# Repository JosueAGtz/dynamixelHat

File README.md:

# RaspberryPi Dynamixel Hat

The Raspberry Pi Zero Dynamixel Hat it's an easy to use hardware that allows you to connect and communicate with Dynamixel Servo Motors by using the Savage Electronics AX interface circuit, providing the half-duplex communication needed by these motors, its implemented in it a voltage converter for all the signals to the Raspberry allowing a secure communication in terms of logical levels.

It also implements a MAX25232ATCG/V+ which is a synchronous step-down DC-DC converter optimized for applications with high power density, This regulator will let you power your Raspberry directly from a battery and also provide power to your motors.

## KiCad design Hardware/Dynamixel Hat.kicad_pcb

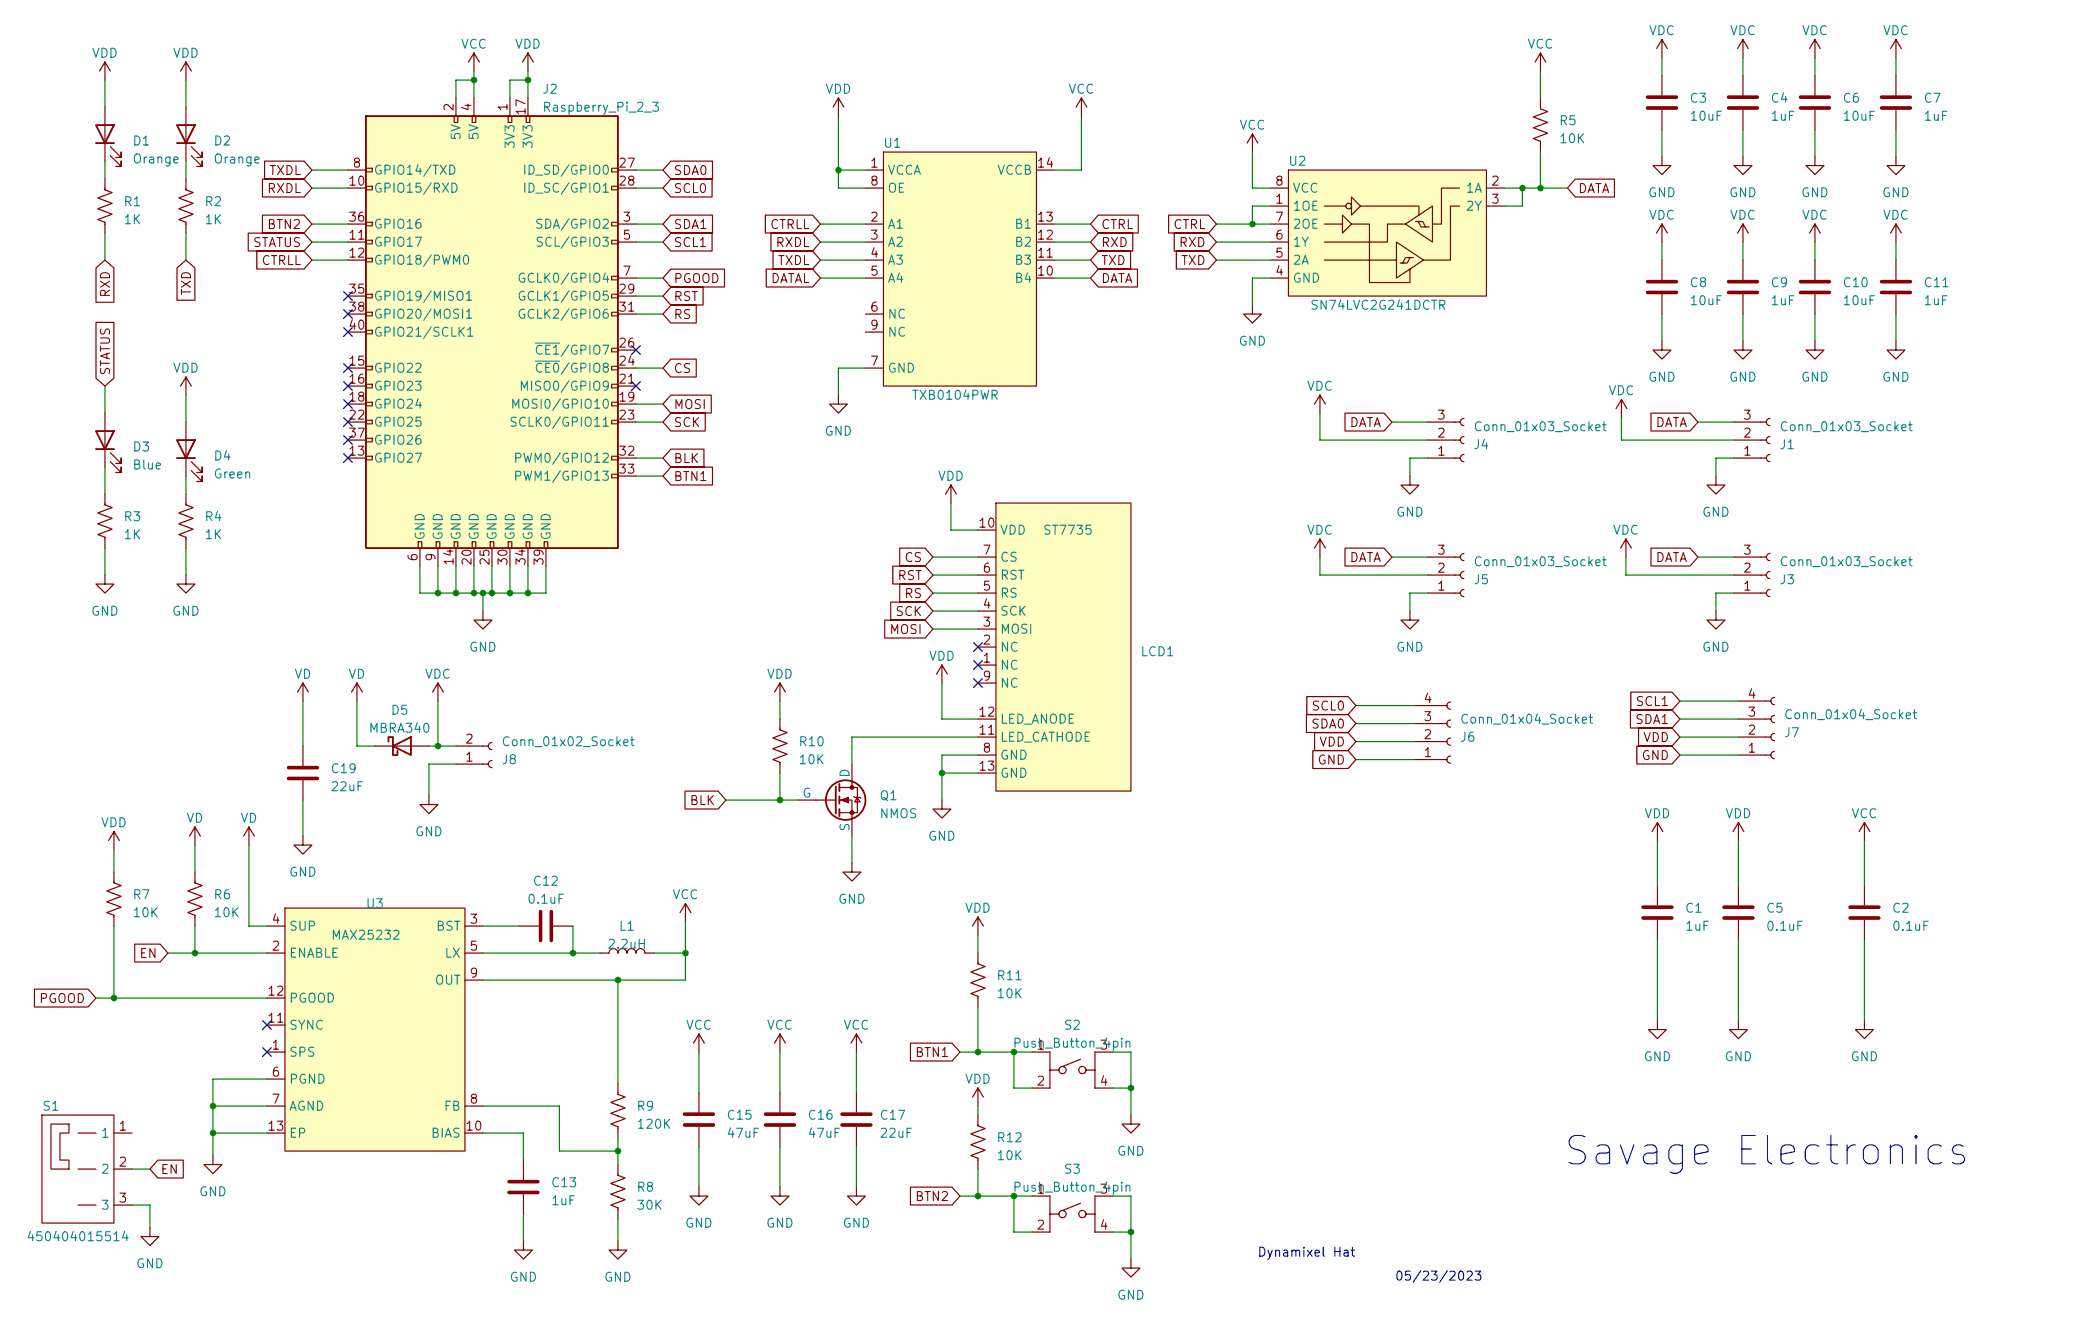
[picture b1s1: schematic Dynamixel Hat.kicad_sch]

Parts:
C1: 1uF; C_0402_1005Metric
C2, C5: 0.1uF; C_0402_1005Metric
C3, C6, C8, C10: 10uF; C_0603_1608Metric
C4, C7, C9, C11, C13: 1uF; C_0603_1608Metric
C12: 0.1uF; C_0603_1608Metric
C15, C16: 47uF; C_1210_3225Metric
C17: 22uF; C_1206_3216Metric
C19: 22uF; C_1210_3225Metric
D1, D2: Orange; 0402LED
D3: Blue; 0402LED
D4: Green; 0402LED
D5: MBRA340; D_SMA
J1, J3, J4, J5: Conn_01x03_Socket; JST_EH_S3B-EH_1x03_P2.50mm_Horizontal
J2: Raspberry_Pi_2_3; Raspberry Pi Zero Hat
J6, J7: Conn_01x04_Socket; JST_SH_SM04B-SRSS-TB_1x04-1MP_P1.00mm_Horizontal
J8: Conn_01x02_Socket; XT60PW-M20
L1: 2.2uH; L_Taiyo-Yuden_MD-5050
LCD1: ST7735; IPS 0.96
Q1: NMOS; SOT-23
R1, R2, R3, R4: 1K; R_0402_1005Metric
R5, R6, R7, R10, R11, R12: 10K; R_0402_1005Metric
R8: 30K; R_0402_1005Metric
R9: 120K; R_0402_1005Metric
S1: 450404015514; 450404015514_SW
S2, S3: Push_Button_4pin; 434123025826
U1: TXB0104PWR; TSSOP14_5x4.4_0.65
U2: SN74LVC2G241DCTR; VSSOP-8_2.3x2mm_P0.5mm
U3: MAX25232; TDFN12_3x3mm_P05_EP

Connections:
BLK: J2.32 (PWM0/GPIO12), Q1.1 (G), R10.2
BTN1: J2.33 (PWM1/GPIO13), R11.2, S2.1, S2.2
BTN2: J2.36 (GPIO16), R12.2, S3.1, S3.2
CS: J2.24 (~CE0/GPIO8), LCD1.7 (CS)
CTRL: U1.13 (B1), U2.1 (1OE), U2.7 (2OE)
CTRLL: J2.12 (GPIO18/PWM0), U1.2 (A1)
DATA: J1.3, J3.3, J4.3, J5.3, R5.2, U1.10 (B4), U2.2 (1A), U2.3 (2Y)
DATAL: U1.5 (A4)
EN: R6.2, S1.2, U3.2 (ENABLE)
GND: C1.2, C2.2, C3.2, C4.2, C5.2, C6.2, C7.2, C8.2, C9.2, C10.2, C11.2, C13.2, C15.2, C16.2, C17.2, C19.2, J1.1, J2.6 (GND), J2.9 (GND), J2.14 (GND), J2.20 (GND), J2.25 (GND), J2.30 (GND), J2.34 (GND), J2.39 (GND), J3.1, J4.1, J5.1, J6.1, J7.1, J8.1, LCD1.8 (GND), LCD1.13 (GND), Q1.2 (S), R3.2, R4.2, R8.2, S1.3, S2.3, S2.4, S3.3, S3.4, U1.7 (GND), U2.4 (GND), U3.6 (PGND), U3.7 (AGND), U3.13 (EP)
MOSI: J2.19 (MOSI0/GPIO10), LCD1.3 (MOSI)
unnamed: D1.1 (K), R1.1
unnamed: D2.1 (K), R2.1
unnamed: D3.1 (K), R3.1
unnamed: D4.1 (K), R4.1
unnamed: LCD1.11 (LED_CATHODE), Q1.3 (D)
unnamed: C13.1, U3.10 (BIAS)
unnamed: C12.1, U3.3 (BST)
unnamed: R8.1, R9.2, U3.8 (FB)
unnamed: C12.2, L1.1, U3.5 (LX)
PGOOD: J2.7 (GCLK0/GPIO4), R7.2, U3.12 (PGOOD)
RS: J2.31 (GCLK2/GPIO6), LCD1.5 (RS)
RST: J2.29 (GCLK1/GPIO5), LCD1.6 (RST)
RXD: R1.2, U1.12 (B2), U2.6 (1Y)
RXDL: J2.10 (GPIO15/RXD), U1.3 (A2)
SCK: J2.23 (SCLK0/GPIO11), LCD1.4 (SCK)
SCL0: J2.28 (ID_SC/GPIO1), J6.4
SCL1: J2.5 (SCL/GPIO3), J7.4
SDA0: J2.27 (ID_SD/GPIO0), J6.3
SDA1: J2.3 (SDA/GPIO2), J7.3
STATUS: D3.2 (A), J2.11 (GPIO17)
TXD: R2.2, U1.11 (B3), U2.5 (2A)
TXDL: J2.8 (GPIO14/TXD), U1.4 (A3)
VCC: C2.1, C15.1, C16.1, C17.1, J2.2 (5V), J2.4 (5V), L1.2, R5.1, R9.1, U1.14 (VCCB), U2.8 (VCC), U3.9 (OUT)
VD: C19.1, D5.1 (K), R6.1, U3.4 (SUP)
VDC: C3.1, C4.1, C6.1, C7.1, C8.1, C9.1, C10.1, C11.1, D5.2 (A), J1.2, J3.2, J4.2, J5.2, J8.2
VDD: C1.1, C5.1, D1.2 (A), D2.2 (A), D4.2 (A), J2.1 (3V3), J2.17 (3V3), J6.2, J7.2, LCD1.10 (VDD), LCD1.12 (LED_ANODE), R7.1, R10.1, R11.1, R12.1, U1.1 (VCCA), U1.8 (OE)

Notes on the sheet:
Dynamixel Hat
05/23/2023
Savage Electronics

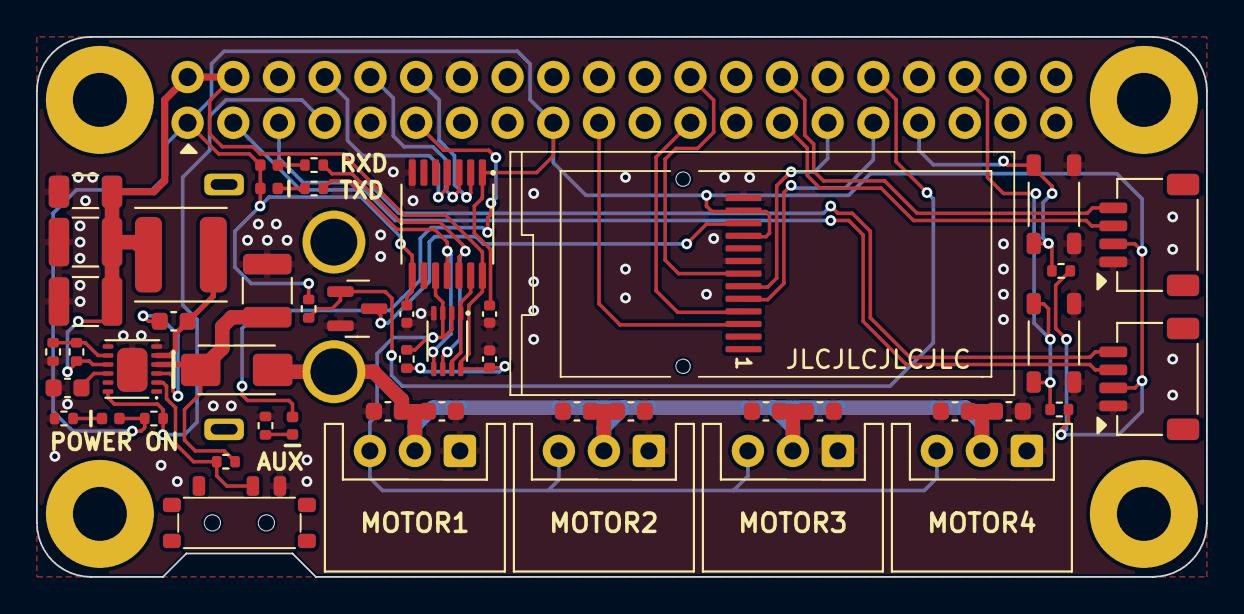
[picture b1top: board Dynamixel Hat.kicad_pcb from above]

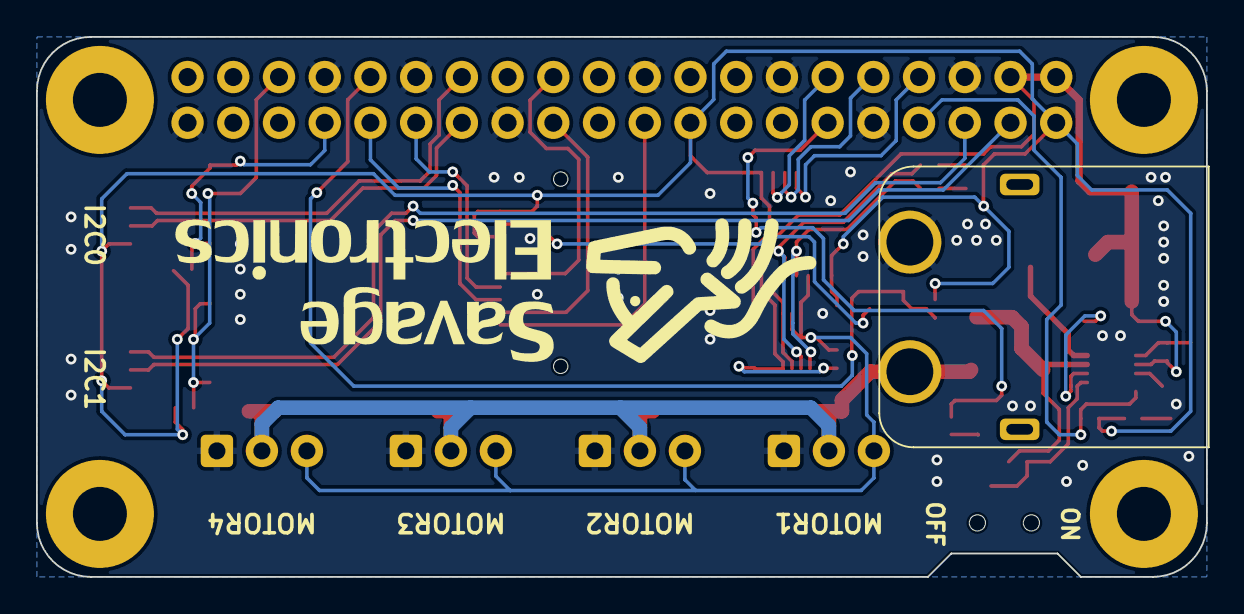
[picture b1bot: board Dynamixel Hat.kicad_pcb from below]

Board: 2 copper layers, 65.0 x 30.0 mm, 52 parts (2 on the bottom side), 36 nets.

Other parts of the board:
G_logoMedium: LOGO; G_SELOGO_MED
